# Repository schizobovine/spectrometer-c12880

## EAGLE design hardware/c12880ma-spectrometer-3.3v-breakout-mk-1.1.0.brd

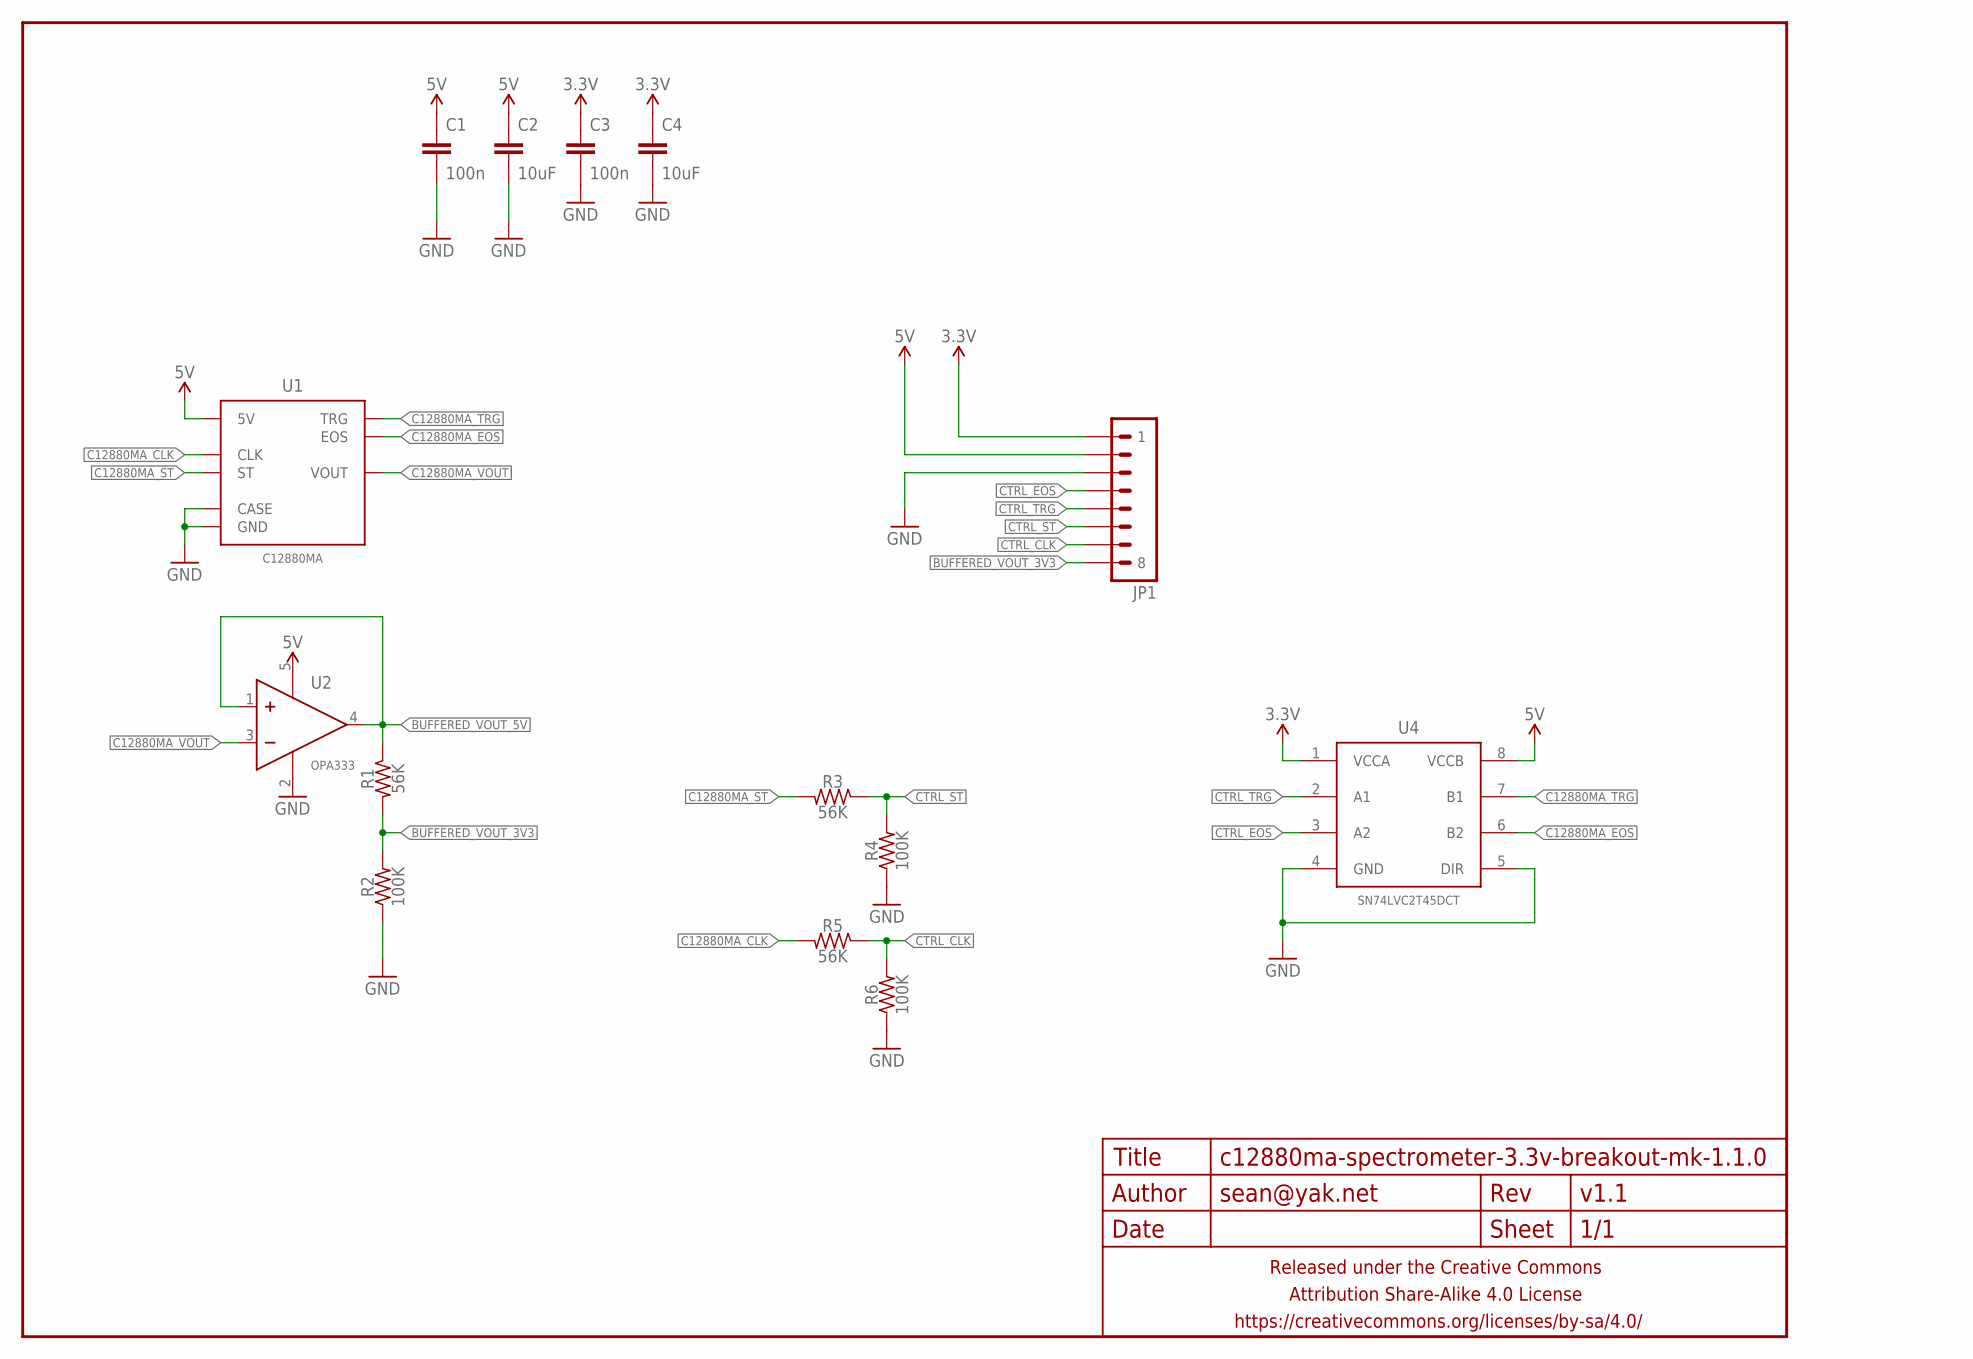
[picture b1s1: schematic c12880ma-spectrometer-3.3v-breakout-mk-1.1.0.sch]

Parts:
C1, C3: 100n; C0402
C2, C4: 10uF; C0603-TIGHTER
FRAME1: FRAME-LETTERNO_PACKAGE; DUMMY
JP1: M081X08; 1X08
R1, R3, R5: 56K; R0402
R2, R4, R6: 100K; R0402
U1: C12880MA; DIL14
U2: OPA333; SC70
U4: SN74LVC2T45DCT; SSOP-8

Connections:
3.3V: C3.1, C4.1, JP1.1, U4.1 (VCCA)
5V: C1.1, C2.1, JP1.2, U1.1 (5V), U1.5 (5V), U2.5 (V+), U4.8 (VCCB)
BUFFERED_VOUT_3V3: JP1.8, R1.2, R2.2
BUFFERED_VOUT_5V: R1.1, U2.1 (IN+), U2.4 (OUT)
C12880MA_CLK: R5.2, U1.6 (CLK)
C12880MA_EOS: U1.13 (EOS), U4.6 (B2)
C12880MA_ST: R3.2, U1.8 (ST)
C12880MA_TRG: U1.9 (TRG), U4.7 (B1)
C12880MA_VOUT: U1.14 (VOUT), U2.3 (IN-)
CTRL_CLK: JP1.7, R5.1, R6.2
CTRL_EOS: JP1.4, U4.3 (A2)
CTRL_ST: JP1.6, R3.1, R4.2
CTRL_TRG: JP1.5, U4.2 (A1)
GND: C1.2, C2.2, C3.2, C4.2, JP1.3, R2.1, R4.1, R6.1, U1.2 (GND), U1.7 (CASE), U2.2 (V-), U4.4 (GND), U4.5 (DIR)

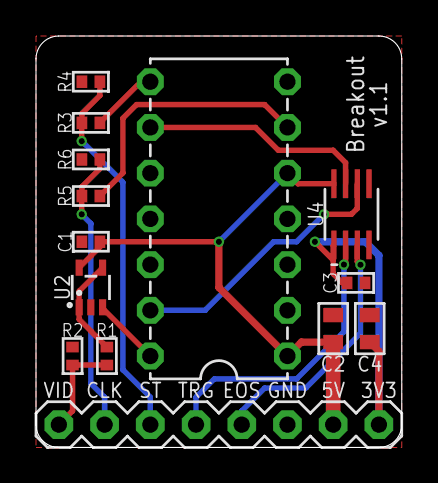
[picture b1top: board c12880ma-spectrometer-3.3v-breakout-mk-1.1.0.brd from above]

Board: 2 copper layers, 20.3 x 22.9 mm, 15 parts (0 on the bottom side), 14 nets.

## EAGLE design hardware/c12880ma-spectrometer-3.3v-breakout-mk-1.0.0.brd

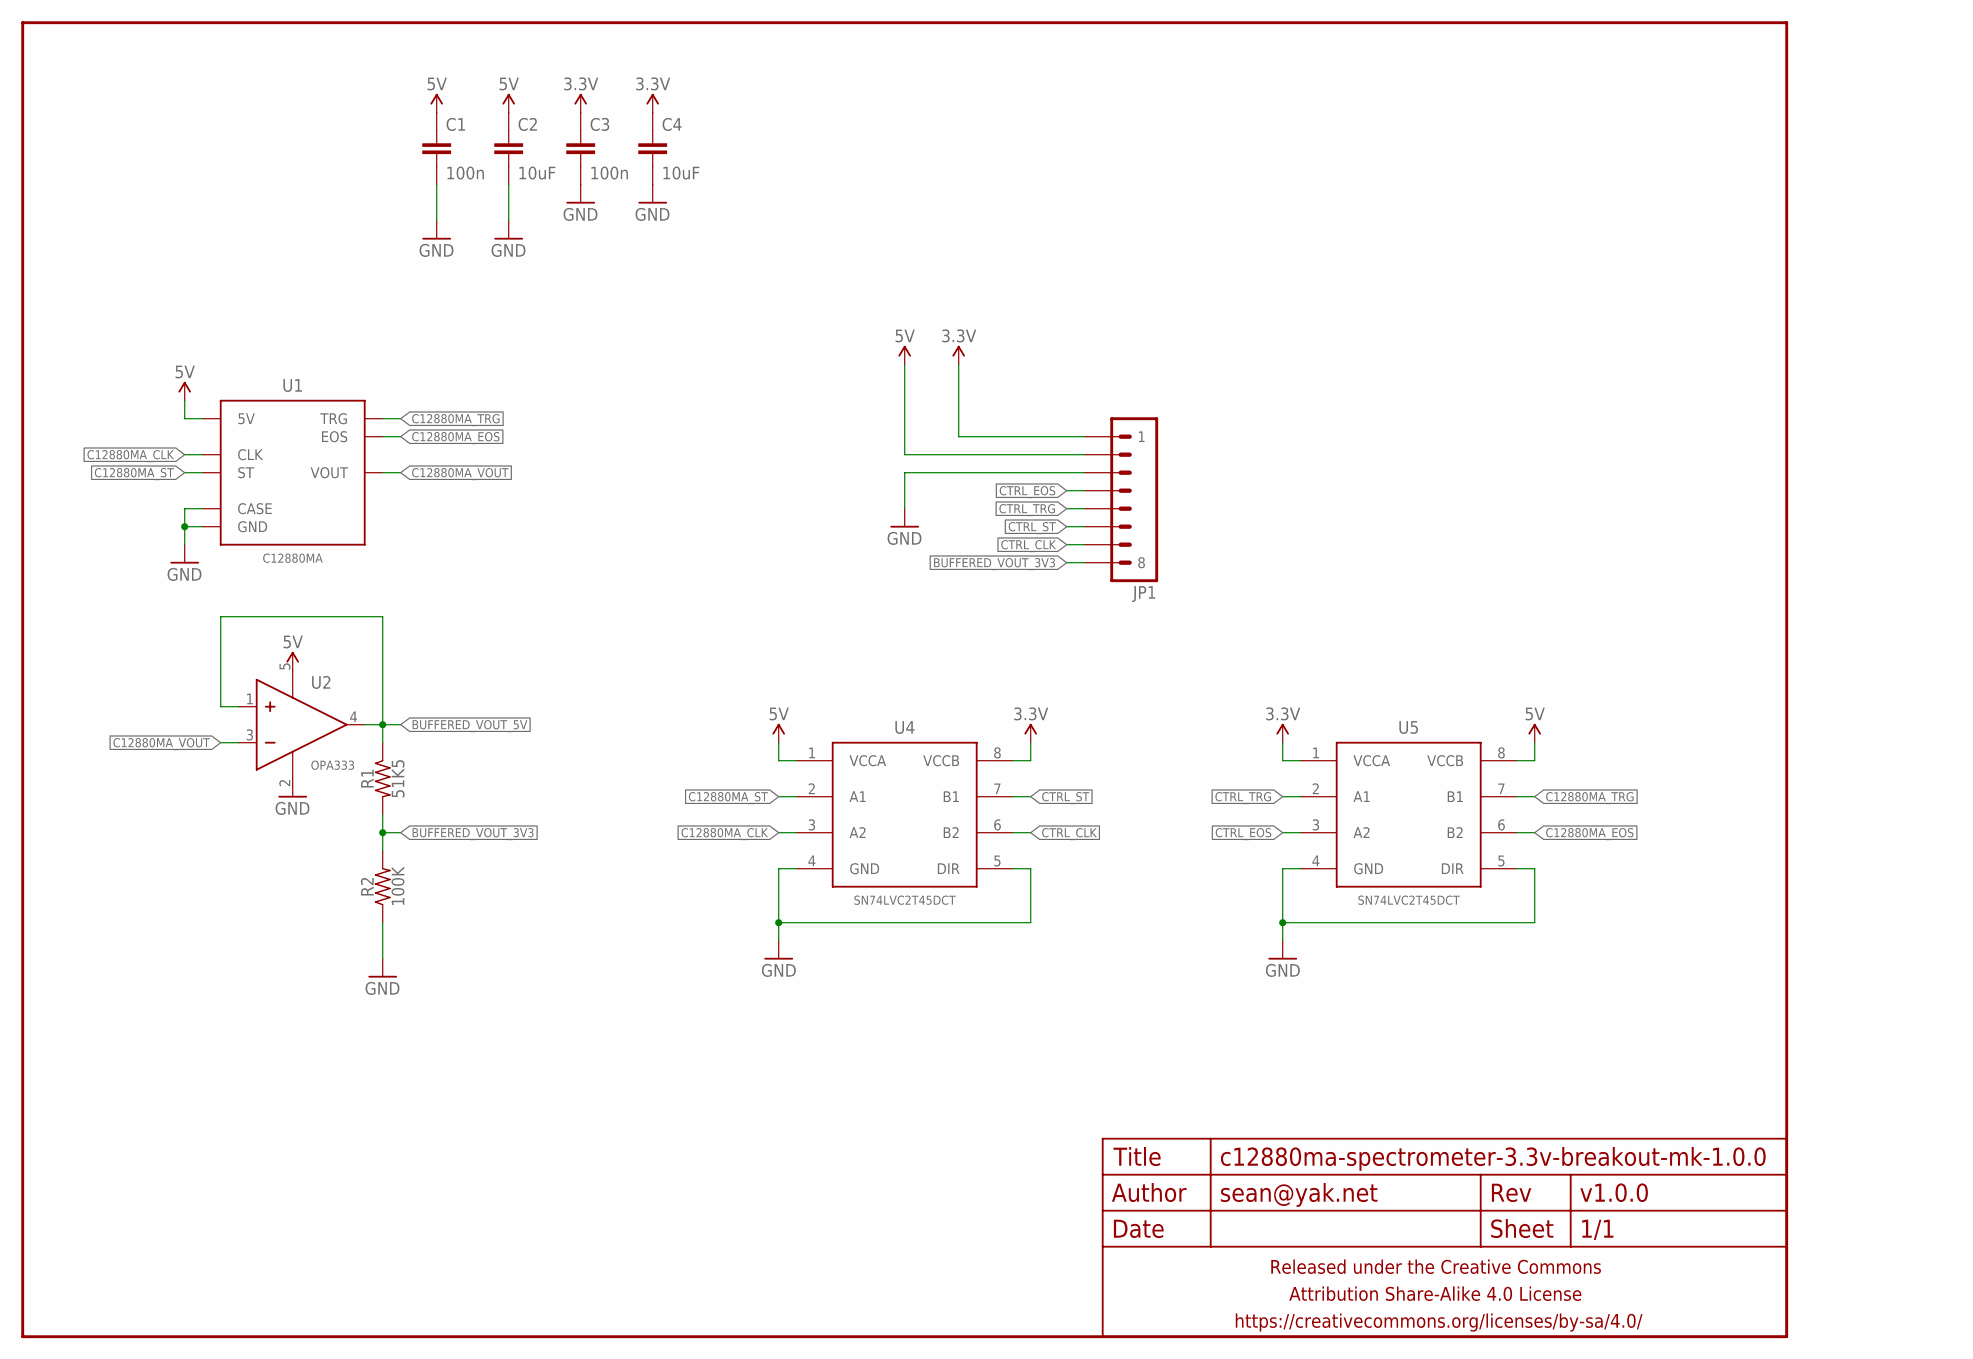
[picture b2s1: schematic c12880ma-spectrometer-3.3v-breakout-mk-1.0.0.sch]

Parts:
C1, C3: 100n; C0402
C2, C4: 10uF; C0603-TIGHTER
FRAME1: FRAME-LETTERNO_PACKAGE; DUMMY
JP1: M081X08; 1X08
R1: 51K5; R0402
R2: 100K; R0402
U1: C12880MA; DIL14
U2: OPA333; SC70
U4, U5: SN74LVC2T45DCT; SSOP-8

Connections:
3.3V: C3.1, C4.1, JP1.1, U4.8 (VCCB), U5.1 (VCCA)
5V: C1.1, C2.1, JP1.2, U1.1 (5V), U1.5 (5V), U2.5 (V+), U4.1 (VCCA), U5.8 (VCCB)
BUFFERED_VOUT_3V3: JP1.8, R1.2, R2.2
BUFFERED_VOUT_5V: R1.1, U2.1 (IN+), U2.4 (OUT)
C12880MA_CLK: U1.6 (CLK), U4.3 (A2)
C12880MA_EOS: U1.13 (EOS), U5.6 (B2)
C12880MA_ST: U1.8 (ST), U4.2 (A1)
C12880MA_TRG: U1.9 (TRG), U5.7 (B1)
C12880MA_VOUT: U1.14 (VOUT), U2.3 (IN-)
CTRL_CLK: JP1.7, U4.6 (B2)
CTRL_EOS: JP1.4, U5.3 (A2)
CTRL_ST: JP1.6, U4.7 (B1)
CTRL_TRG: JP1.5, U5.2 (A1)
GND: C1.2, C2.2, C3.2, C4.2, JP1.3, R2.1, U1.2 (GND), U1.7 (CASE), U2.2 (V-), U4.4 (GND), U4.5 (DIR), U5.4 (GND), U5.5 (DIR)

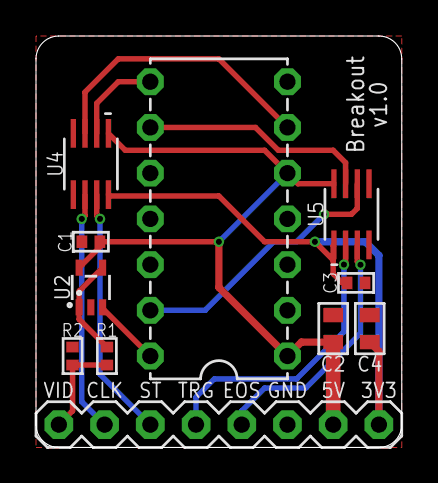
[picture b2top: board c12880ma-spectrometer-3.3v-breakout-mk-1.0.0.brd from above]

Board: 2 copper layers, 20.3 x 22.9 mm, 12 parts (0 on the bottom side), 14 nets.

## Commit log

2019-11-10 rearrange repo
2019-11-10 first two breakouts for 3.3V microcontrollers
2019-11-10 strip out unneeded parts
2019-11-10 rename so arduino doesn't complain
2019-11-10 more modifications and copying in the elapseMilis header file because i am lazy"

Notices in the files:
parts and their libraries:
a_parts: Released under the Creative Commons Attribution Share-Alike 4.0 License
a_parts: https://creativecommons.org/licenses/by-sa/4.0
a_parts: Released under the Creative Commons
